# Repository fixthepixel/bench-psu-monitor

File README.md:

# Bench PSU Monitor

A 3-channel bench power supply monitor PCB built around an **ESP32 DevKit V1** and a **Texas Instruments INA3221** triple-channel current/voltage sense IC.

## Features

- 3 independent measurement channels (CH1, CH2, CH3) via screw terminals
- Voltage and current monitoring over I²C using the INA3221
- 10 mΩ shunt resistors for current sensing
- I²C address selection via solder jumpers JP1/JP2
- Compact 2-layer PCB with gerbers ready for fabrication

## Interactive BOM

[View Interactive BOM](https://fixthepixel.github.io/bench-psu-monitor/bom/ibom.html)

## Hardware

| Component | Value / Part |
|-----------|-------------|
| MCU | ESP32 DevKit V1 (30-pin) |
| Current/Voltage monitor | INA3221 (3-channel, I²C) |
| Shunt resistors | 10 mΩ (RS1, RS2, RS3) |
| Bypass capacitor | 100 nF |
| Bulk capacitor | 10 µF |

## Repository Contents

```
bench-psu-monitor.kicad_sch   Schematic
bench-psu-monitor.kicad_pcb   PCB layout
bom/ibom.html                 Interactive BOM
gerber/                       Gerber files for fabrication
firmware/                     ESP32 Arduino sketch
```

See [firmware/README.md](firmware/README.md) for flashing instructions, library dependencies, and WebSocket API reference.

## Fabrication

Gerber files are in [gerber/](gerber/) and can be sent directly to any PCB manufacturer. The board is 2-layer (F_Cu / B_Cu).

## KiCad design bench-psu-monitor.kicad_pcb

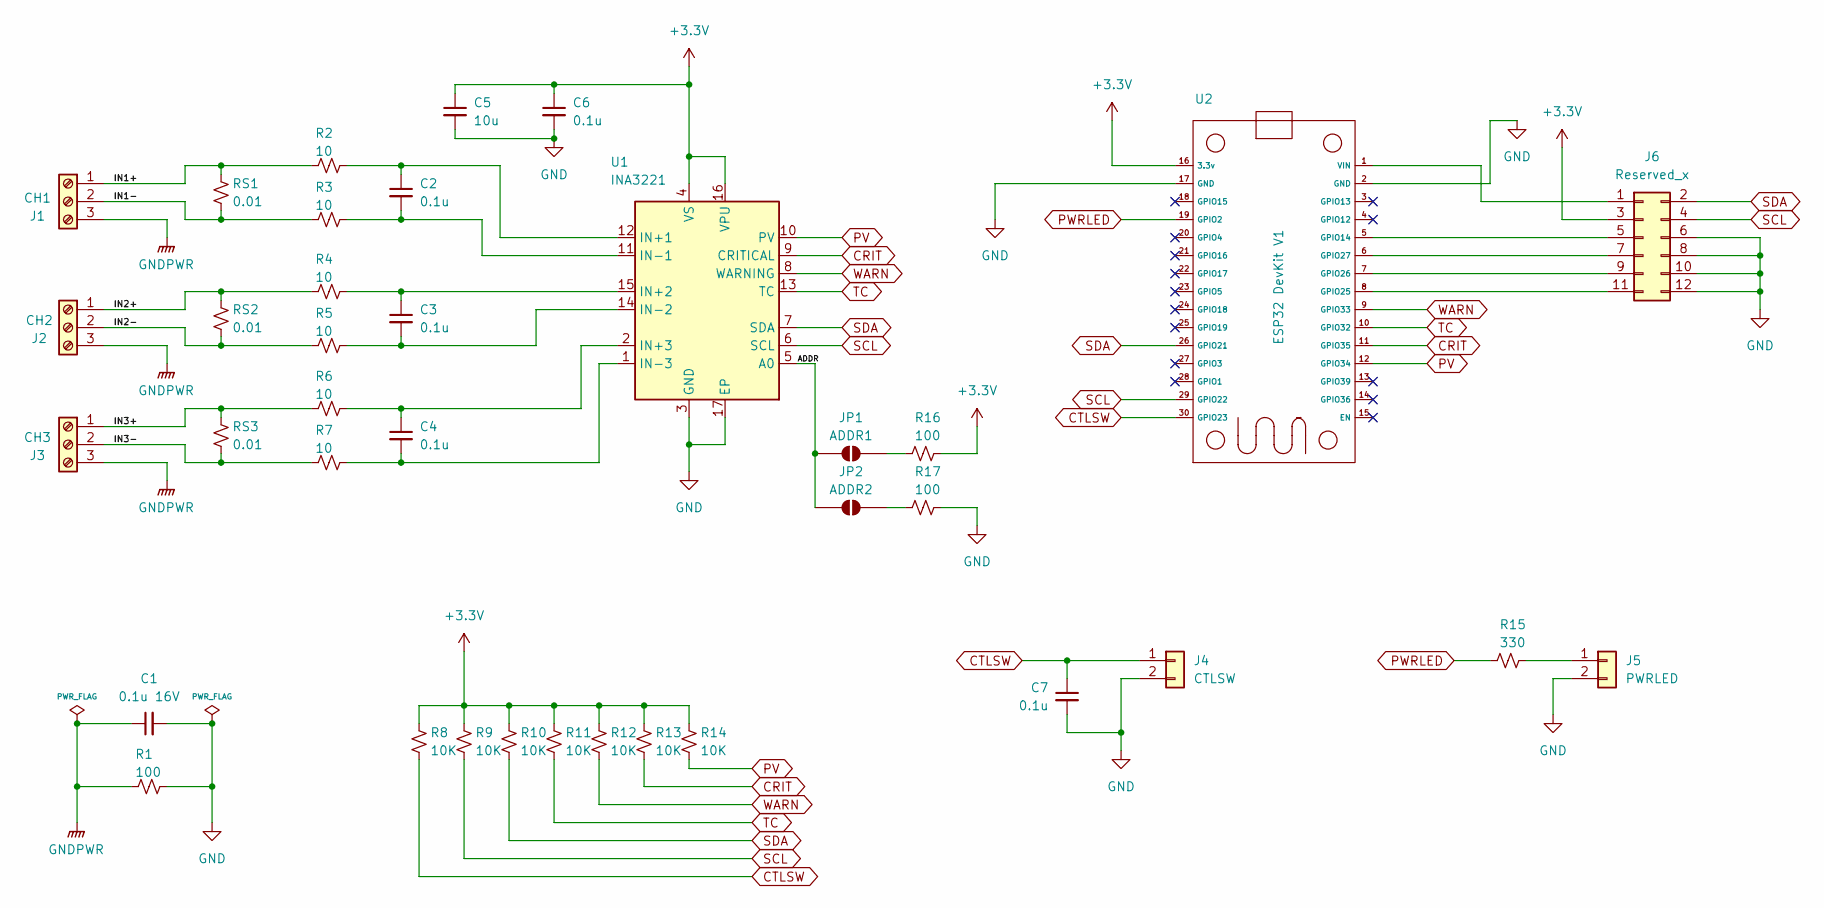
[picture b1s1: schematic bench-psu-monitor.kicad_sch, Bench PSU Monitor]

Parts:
C1: 0.1u 16V; C_1206_3216Metric
C2, C3, C4, C6, C7: 0.1u; C_1206_3216Metric
C5: 10u; C_1206_3216Metric
J1: CH1; TerminalBlock_Phoenix_PT-1,5-3-5.0-H_1x03_P5.00mm_Horizontal
J2: CH2; TerminalBlock_Phoenix_PT-1,5-3-5.0-H_1x03_P5.00mm_Horizontal
J3: CH3; TerminalBlock_Phoenix_PT-1,5-3-5.0-H_1x03_P5.00mm_Horizontal
J4: CTLSW; JST_XH_B2B-XH-A_1x02_P2.50mm_Vertical
J5: PWRLED; JST_XH_B2B-XH-A_1x02_P2.50mm_Vertical
J6: Reserved_x; PinSocket_2x06_P2.54mm_Vertical
JP1: ADDR1; SolderJumper-2_P1.3mm_Open_RoundedPad1.0x1.5mm
JP2: ADDR2; SolderJumper-2_P1.3mm_Open_RoundedPad1.0x1.5mm
R1: 100; R_0603_1608Metric
R2, R3, R4, R5, R6, R7: 10; R_0603_1608Metric
R8, R9, R10, R11, R12, R13, R14: 10K; R_1206_3216Metric
R15: 330; R_1206_3216Metric
R16, R17: 100; R_1206_3216Metric
RS1, RS2, RS3: 0.01; R_2512_6332Metric
U1: INA3221; Texas_RGV0016A_VQFN-16-1EP_4x4mm_P0.65mm_EP2.1x2.1mm
U2: ESP32 DevKit V1; ESP32_30pin

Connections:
+3.3V: C5.1, C6.1, J6.3, R8.1, R9.1, R10.1, R11.1, R12.1, R13.1, R14.1, R16.2, U1.4 (VS), U1.16 (VPU), U2.16 (3.3v)
/ADDR: JP1.1 (A), JP2.1 (A), U1.5 (A0)
/IN1+: J1.1, R2.1, RS1.1
/IN1-: J1.2, R3.1, RS1.2
/IN2+: J2.1, R4.1, RS2.1
/IN2-: J2.2, R5.1, RS2.2
/IN3+: J3.1, R6.1, RS3.1
/IN3-: J3.2, R7.1, RS3.2
CRIT: R13.2, U1.9 (CRITICAL), U2.11 (GPIO35)
CTLSW: C7.1, J4.1, R8.2, U2.30 (GPIO23)
GND: C1.2, C5.2, C6.2, C7.2, J4.2, J5.2, J6.6, J6.8, J6.10, J6.12, R1.2, R17.2, U1.3 (GND), U1.17 (EP), U2.2 (GND), U2.17 (GND)
GNDPWR: C1.1, J1.3, J2.3, J3.3, R1.1
unnamed: J5.1, R15.2
unnamed: J6.1, U2.1 (VIN)
unnamed: J6.5, U2.5 (GPIO14)
unnamed: J6.7, U2.6 (GPIO27)
unnamed: J6.9, U2.7 (GPIO26)
unnamed: J6.11, U2.8 (GPIO25)
unnamed: JP1.2 (B), R16.1
unnamed: JP2.2 (B), R17.1
unnamed: C2.1, R2.2, U1.12 (IN+1)
unnamed: C3.1, R4.2, U1.15 (IN+2)
unnamed: C4.1, R6.2, U1.2 (IN+3)
unnamed: C2.2, R3.2, U1.11 (IN-1)
unnamed: C3.2, R5.2, U1.14 (IN-2)
unnamed: C4.2, R7.2, U1.1 (IN-3)
PV: R14.2, U1.10 (PV), U2.12 (GPIO34)
PWRLED: R15.1, U2.19 (GPIO2)
SCL: J6.4, R9.2, U1.6 (SCL), U2.29 (GPIO22)
SDA: J6.2, R10.2, U1.7 (SDA), U2.26 (GPIO21)
TC: R11.2, U1.13 (TC), U2.10 (GPIO32)
WARN: R12.2, U1.8 (WARNING), U2.9 (GPIO33)

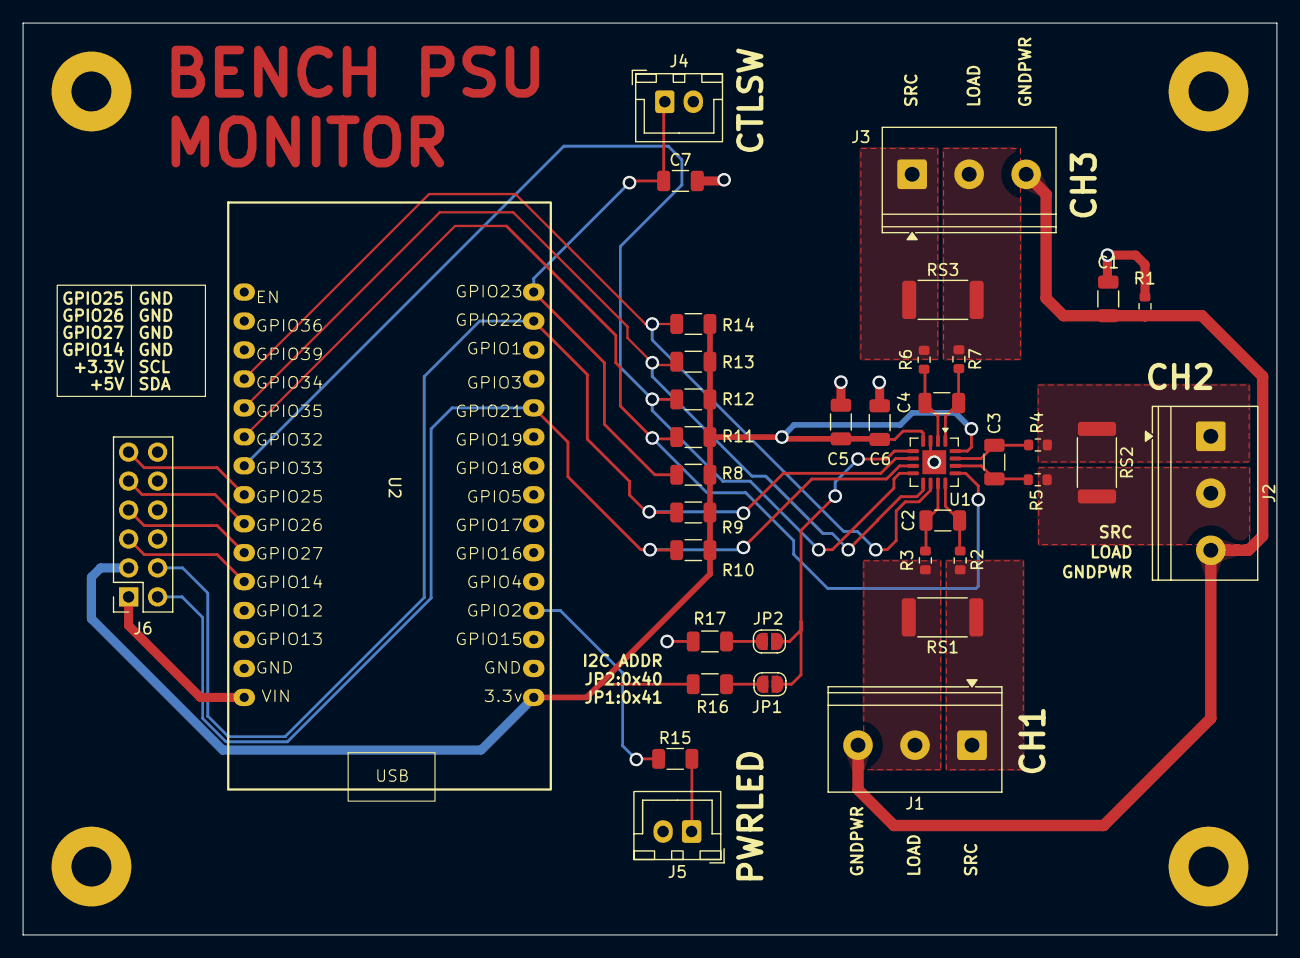
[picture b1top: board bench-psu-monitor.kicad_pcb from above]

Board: 2 copper layers, 110.0 x 80.0 mm, 37 parts (0 on the bottom side), 32 nets.
